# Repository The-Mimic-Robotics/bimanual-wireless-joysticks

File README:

)

## Summary

This project enables the high-precision wireless control of MISC, two robotic arms, using Feetech STS smart motors. By utilizing a distributed architecture of ESP32 microcontrollers, the system translates physical joystick inputs into real-time robotic movement, with XBOX controller protocol emulation.

It is designed for low latency and high reliability, featuring a central hub that aggregates data from multiple peripheral devices to synchronize motor behavior across a daisy-chained serial bus.

## Features

### Multi-Protocol Wireless Control

Leverages **ESP-NOW** to transmit joystick data from peripheral ESP32-C3 SuperMini units to a central hub with sub-second processing latency and **Bluetooth Low Energy (BLE)** to relay the combined data to a workstation.

### BOX Protocol Emulation

The central ESP32 Node-MCU formats incoming data to impersonate standard XBOX controller protocols using **jsTest**, allowing the robotic inputs to be recognized by standard simulation and gaming software.

### Daisy-Chained Smart Servos

Controls a series of 4 **Feetech STS smart motors** via a single UART interface, maximizing hardware efficiency while maintaining individual motor addressability. Only visible [here](https://projectgrid.net/museum/mimicbrach)!

### Precision Calibration

Includes a dedicated calibration suite using potentiometers to record non-zero offsets and an algorithmic safety layer to enforce the unique range of motion for each specific motor.

### Functional Block Architecture

Components are grouped into logical clusters (Power, Processing, IO), significantly reducing the "Spaghetti Ratsnest" effect and shortening signal paths for improved electromagnetic compatibility (EMC).

### Advanced Power Filtering

Features a precision decoupling strategy with 0.1uF and 22uF local energy reservoirs placed at the physical limit of the VCC pins to prevent high-frequency noise and random system crashes.

### Thermal Heat Sinking

Utilizes strategic copper pours and ground planes to act as a passive heat sink for the L7805 regulator, preventing thermal shutdown in high-current applications.

### Fabrication-Ready Constraints

Incorporates strict design rules for copper-to-edge clearances and mechanical "finger space," ensuring the board is both manufacturable and usable in real-world enclosures.

## Technical Implementation

The architecture is split between input capture and central processing to minimize cumulative latency:

### Peripheral Input (ESP32-C3 SuperMini)

Acts as the peripheral device for reading analog joystick inputs. It handles the initial signal processing and transmits the data packets wirelessly to the hub. It also supports a serial bridge for real-time robotic arm simulations.

### Central Hub (ESP32 Node-MCU)

Aggregates data from both peripheral arms, handles the logic for motor ID deduction in daisy-chained configurations, and outputs the final formatted control signals.

### Hardware & Power Management

* **Communication:** UART protocol for high-speed motor telemetry.
* **Power:** Powered by a programmable DC supply outputting **7.4V @ 2A**, optimized for the peak current draw of 4 smart motors.
* **Latency Control:** Rigorous experimental tuning using 3D-printed mini robot arms to ensure 100% mirroring of user inputs.

### Functional Grouping & Routing

To avoid a "Spaghetti" ratsnest, MicroNode utilizes functional block grouping. All capacitors and resistors for the ESP32 are kept in close proximity to the MCU, while the L7805 and its filter capacitors form a dedicated power block. Components are rotated to minimize crossing "ratsnest" lines, resulting in shorter, straighter traces.

### Local Energy Reservoirs

Electrical stability is maintained by placing the 0.1uF decoupling capacitor as close as physically possible to the VCC pin of the ESP32. This creates the shortest possible VCC-Capacitor-Ground loop, allowing the capacitor to filter high-frequency noise effectively.

### Edge Clearance Constraints

To prevent the fabrication house's router bits from clipping copper traces, a "Copper to Edge" clearance of 0.5mm (20 mils) is enforced via KiCad’s Design Rules (Board Setup > Constraints). This protects the integrity of the yellow Edge.Cuts boundary during the milling process.

### Thermal Management (L7805)

The L7805 linear regulator is given "breathing room" to convert excess voltage into heat safely. Instead of smothering it between larger components, it is connected to a large Ground Plane (Copper Pour) which pulls heat away from the regulator body.

### Mechanical & 3D Verification

The KiCad 3D Viewer (Alt + 3) is used to verify "Finger Space." This ensures that connectors are not placed so close together that cables cannot be plugged in, and that tall components do not obstruct mechanical access.

## Installation

### Clone the project repository

```bash
git clone https://github.com/The-Mimic-Robotics/bimanual-wireless-joysticks.git
```

### Peripheral (ESP32-C3 SuperMini)

#### Install the libraries

#### Upload Peripheral Code

1. Connect the ESP32-C3 SuperMini.
2. Change the BOARD_ID integer value!
3. Flash the device.

### Central Hub (ESP32 Node-MCU)

#### Install the libraries

#### Upload Central Hub Code

1. Connect the ESP32 Node-MCU.
2. Flash the device.

### Smart Motors Controller

#### Install the libraries

#### Upload [Code](https://projectgrid.net/museum/mimicbrach)

1. Connect the desired micro-controller
2. Flash the device.

## Authors

|Maintainer|Gabrel Oliveira da Silva
|------------|-------------------------
|Status|Maintained/Active
|Web-Page|https://projectgrid.net
|Patch Work|https://github.com/The-Mimic-Robotics/bimanual-wireless-joysticks/commits?author=gabibdods
|SCM|https://github.com/The-Mimic-Robotics/bimanual-wireless-joysticks.git
|Files|ble_central/, ble_periph/, control_servo/, .tool-versions

|Maintainer|Ashal Patel
|------------|-------------------------
|Status|Maintained/Contributing
|Web-Page|https://portfolio-website-alpha-smoky-75.vercel.app
|Patch Work|https://github.com/The-Mimic-Robotics/bimanual-wireless-joysticks/commits?author=ac-pate
|SCM|https://github.com/The-Mimic-Robotics/bimanual-wireless-joysticks.git
|Files|imu_wt61/

## Album

### Network of micro-controllers

### And more!

[Here!](https://projectgrid.net/mimicbrach)

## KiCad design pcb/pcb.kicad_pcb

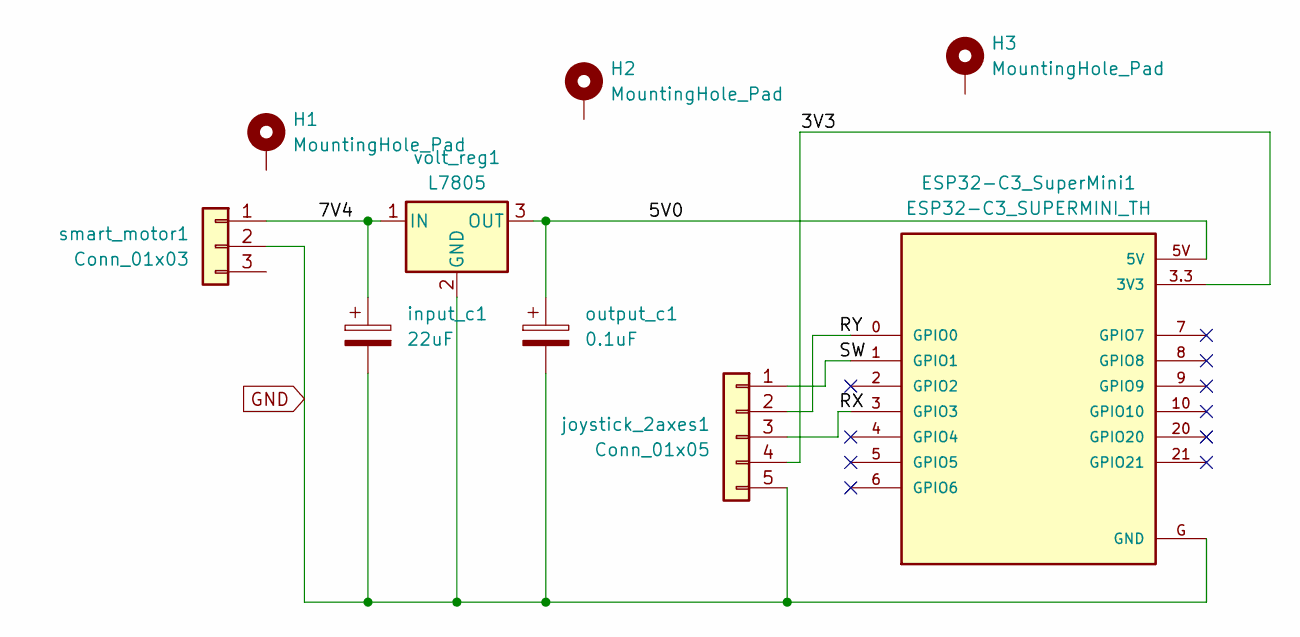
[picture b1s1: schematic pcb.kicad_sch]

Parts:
ESP32-C3_SuperMini1: ESP32-C3_SUPERMINI_TH; MODULE_ESP32-C3_SUPERMINI_TH
H1, H2, H3: MountingHole_Pad; MountingHole_2.5mm_Pad
input_c1: 22uF; CP_Radial_D6.3mm_P2.50mm
joystick_2axes1: Conn_01x05; PinHeader_1x05_P2.54mm_Vertical
output_c1: 0.1uF; CP_Radial_D4.0mm_P2.00mm
smart_motor1: Conn_01x03; PinHeader_1x03_P2.54mm_Vertical
volt_reg1: L7805; TO-220-3_Vertical

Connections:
/3V3: ESP32-C3_SuperMini1.3.3 (3V3), joystick_2axes1.4 (5V)
/5V0: ESP32-C3_SuperMini1.5V, output_c1.1, volt_reg1.3 (OUT)
/7V4: input_c1.1, smart_motor1.1 (7V4), volt_reg1.1 (IN)
/RX: ESP32-C3_SuperMini1.3 (GPIO3), joystick_2axes1.3 (Rx)
/RY: ESP32-C3_SuperMini1.0 (GPIO0), joystick_2axes1.2 (Ry)
/SW: ESP32-C3_SuperMini1.1 (GPIO1), joystick_2axes1.1 (SW)
GND: ESP32-C3_SuperMini1.G (GND), input_c1.2, joystick_2axes1.5 (GND), output_c1.2, smart_motor1.2 (GND), volt_reg1.2 (GND)

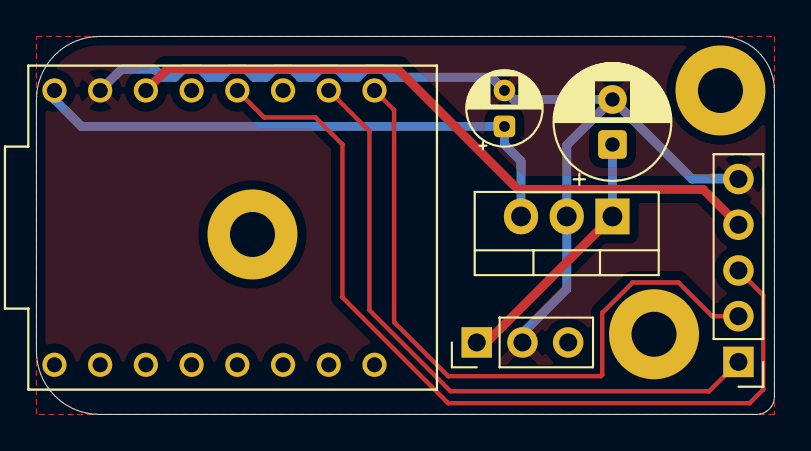
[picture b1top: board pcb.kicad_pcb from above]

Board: 2 copper layers, 41.0 x 21.0 mm, 9 parts (0 on the bottom side), 7 nets.

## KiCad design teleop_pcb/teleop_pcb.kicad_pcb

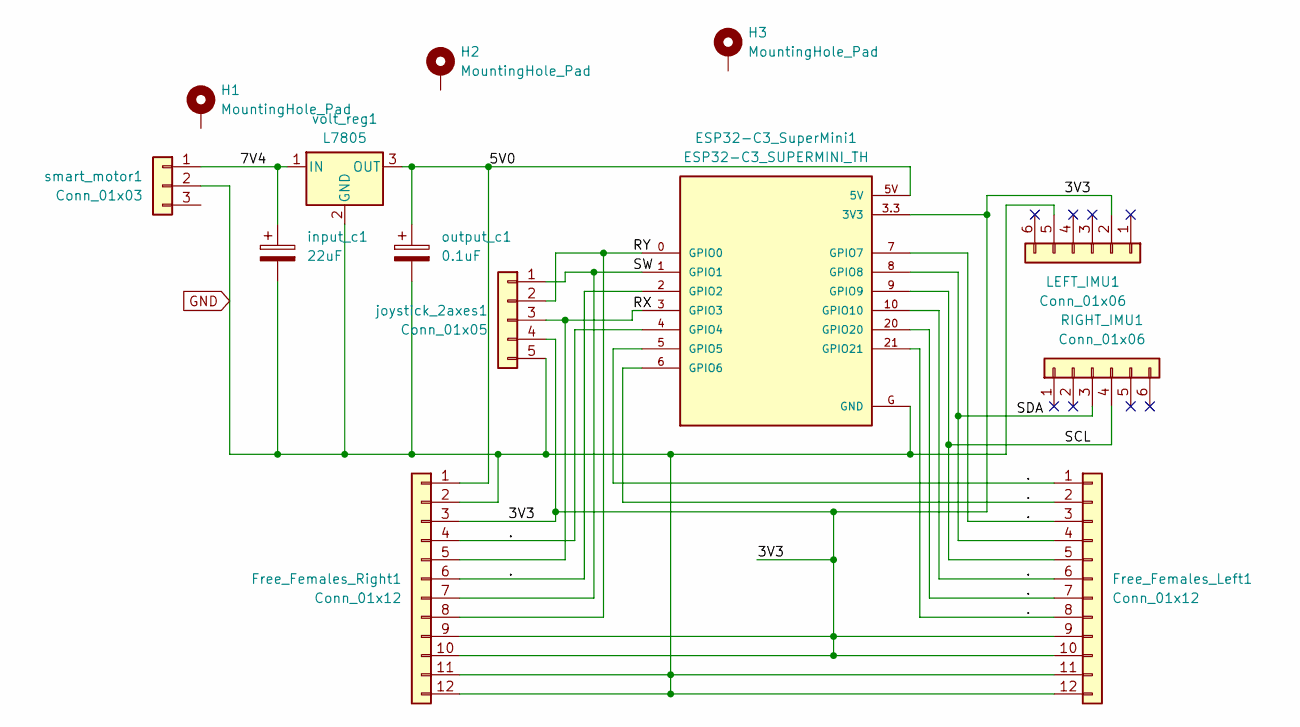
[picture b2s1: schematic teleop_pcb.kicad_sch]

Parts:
ESP32-C3_SuperMini1: ESP32-C3_SUPERMINI_TH; MODULE_ESP32-C3_SUPERMINI_TH
Free_Females_Left1: Conn_01x12; PinSocket_1x12_P2.54mm_Vertical
Free_Females_Right1: Conn_01x12; PinSocket_1x12_P2.54mm_Vertical
H1, H2, H3: MountingHole_Pad; MountingHole_2.5mm_Pad
LEFT_IMU1: Conn_01x06; PinSocket_1x06_P2.54mm_Vertical
RIGHT_IMU1: Conn_01x06; PinSocket_1x06_P2.54mm_Vertical
input_c1: 22uF; CP_Radial_D6.3mm_P2.50mm
joystick_2axes1: Conn_01x05; PinHeader_1x05_P2.54mm_Vertical
output_c1: 0.1uF; CP_Radial_D4.0mm_P2.00mm
smart_motor1: Conn_01x03; PinHeader_1x03_P2.54mm_Vertical
volt_reg1: L7805; TO-220-3_Vertical

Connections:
/3V3: ESP32-C3_SuperMini1.3.3 (3V3), Free_Females_Left1.9, Free_Females_Left1.10, Free_Females_Right1.3, Free_Females_Right1.9, Free_Females_Right1.10, LEFT_IMU1.2 (VCC), joystick_2axes1.4 (5V)
/5V0: ESP32-C3_SuperMini1.5V, Free_Females_Right1.1, output_c1.1, volt_reg1.3 (OUT)
/7V4: input_c1.1, smart_motor1.1 (7V4), volt_reg1.1 (IN)
/.: ESP32-C3_SuperMini1.2 (GPIO2), ESP32-C3_SuperMini1.4 (GPIO4), ESP32-C3_SuperMini1.5 (GPIO5), ESP32-C3_SuperMini1.6 (GPIO6), ESP32-C3_SuperMini1.7 (GPIO7), ESP32-C3_SuperMini1.10 (GPIO10), ESP32-C3_SuperMini1.20 (GPIO20), ESP32-C3_SuperMini1.21 (GPIO21), Free_Females_Left1.1, Free_Females_Left1.2, Free_Females_Left1.3, Free_Females_Left1.6, Free_Females_Left1.7, Free_Females_Left1.8, Free_Females_Right1.4, Free_Females_Right1.6
/RX: ESP32-C3_SuperMini1.3 (GPIO3), Free_Females_Right1.5, joystick_2axes1.3 (Rx)
/RY: ESP32-C3_SuperMini1.0 (GPIO0), Free_Females_Right1.8, joystick_2axes1.2 (Ry)
/SCL: ESP32-C3_SuperMini1.9 (GPIO9), Free_Females_Left1.5, RIGHT_IMU1.4
/SDA: ESP32-C3_SuperMini1.8 (GPIO8), Free_Females_Left1.4, RIGHT_IMU1.3
/SW: ESP32-C3_SuperMini1.1 (GPIO1), Free_Females_Right1.7, joystick_2axes1.1 (SW)
GND: ESP32-C3_SuperMini1.G (GND), Free_Females_Left1.11, Free_Females_Left1.12, Free_Females_Right1.2, Free_Females_Right1.11, Free_Females_Right1.12, LEFT_IMU1.5 (GND), input_c1.2, joystick_2axes1.5 (GND), output_c1.2, smart_motor1.2 (GND), volt_reg1.2 (GND)

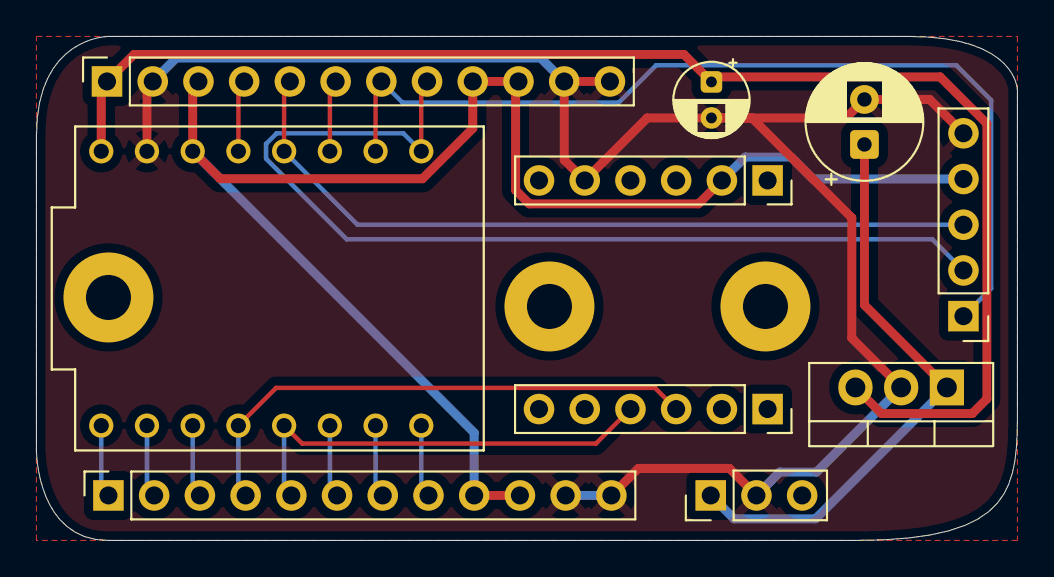
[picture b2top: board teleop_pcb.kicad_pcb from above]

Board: 2 copper layers, 54.5 x 28.0 mm, 13 parts (0 on the bottom side), 10 nets.

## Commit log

2026-01-04 dataflow change: 2 peripherals sending joystick data to central device
2026-01-10 jstest reads 4 axes from 0 to 4095
2026-01-14 reorganized repo structure with platform.io
2026-01-14 reorganized better repo structure
2026-01-15 platform.io uses core 2.x.x instead of 3.x.x
2026-01-15 pin 3 of ESP32-C3 SuperMini is faulty, switch to pin 0
2026-01-15 added python script to emulate joysticks inputs
2026-01-16 fixed crashing python emulator by downloading python 3.12.12
2026-01-18 minimized python emu
2026-01-19 fixed inversed axes of left joystick display
2026-01-20 ADDS: IMU sample code for quat. data over I2C
2026-01-21 first attempt at PCB designing
2026-01-21 added safeguard to ble_central; added delay to ble_periph
2026-01-21 removed tracking for pcb/pcb-backups/
2026-01-21 added ground plane on front and back of pcb
2026-01-24 new pcb with custom footprint
2026-01-24 added rounded edges, mounting holes and legend on pcb
2026-01-28 teleop pcb with place for IMU
2026-02-01 added pin socket rows for teleop pcb
2026-02-28 periph sending BLE signals to specific MAC of central hub does not work
2026-03-26 added deadzone for ble peripherals
2026-03-26 increased deadzone
